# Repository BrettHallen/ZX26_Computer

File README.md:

# ZX26 Computer
I thought it might be interested to have a crack at designing a simple ZX81 clone that utilised the services of the vLA81.<br>

## [Issue 1](/Issue1)
This is my first attempt, just to see if it'll work.  I have left off the expansion connector for now.<br>

The design includes:
- Gateron low-profile keyswitches
- Dedicated cursor key cluster
- Atari-compatible joystick interface
- "FIRE" selectable between ZERO and SPACE keys
- 32KB of RAM (three schemes selectable via vLA81)
- 32KB of ROM (four switchable 8KB banks, i.e. original BASIC, modernised BASIC, ASZMIC assembler, ZX81 FORTH)
- 5V power in using a USB Type B connector (nice 'n' solid)
- Baseband video output selectable between NTSC (USA) and PAL (UK)

## vLA81
Utilising [VRetro's modern ULA replacement](https://www.vretrodesign.com/products/vla81-zx81-ula-replacement) to simplify parts & design.<br>

## Parts
Refer to the BOM for all parts.<br>

Some specific parts (i.e. footprints) I've utilised are:
- USB Type B: Same Sky UJ2-B-HR-G-TH
- RCA Jack: Kobiconn 156-0099-E
- 3.5mm Mono Jack: Same Sky SJ3-350820B
- DE9 Plug: Amphenol L717SDE09PA4CH4FC309 (or similar)

## Useful Information
- https://oldcomputer.info/8bit/zx81/ULA/ula.htm
- https://hackaday.io/project/192473-zx80zx81-remakes

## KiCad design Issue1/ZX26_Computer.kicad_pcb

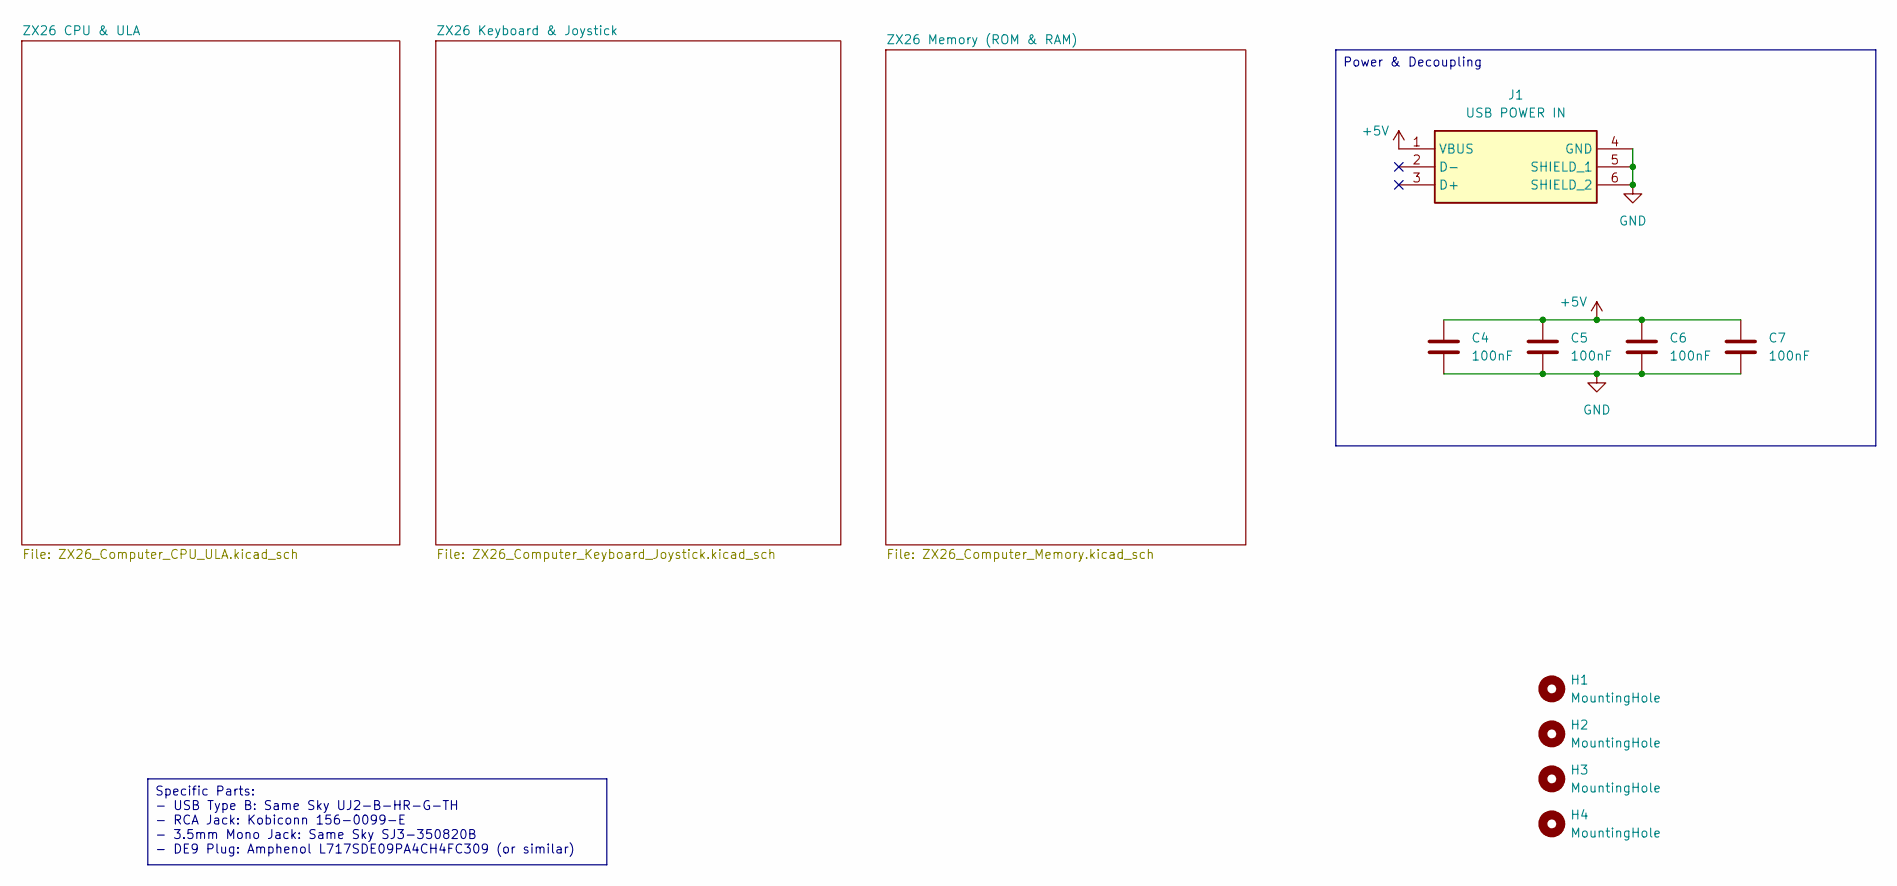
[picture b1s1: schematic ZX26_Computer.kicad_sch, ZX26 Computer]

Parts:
C4, C5, C6, C7: 100nF; C_Disc_D3.8mm_W2.6mm_P2.50mm
H1, H2, H3, H4: MountingHole; MountingHole_3.2mm_M3
J1: USB POWER IN; UJ2BHRGTH; Mouser Part Number 179-UJ2-B-HR-G-TH

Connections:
+5V: C4.1, C5.1, C6.1, C7.1, J1.1 (VBUS); also elsewhere on the board
GND: C4.2, C5.2, C6.2, C7.2, J1.4 (GND), J1.5 (SHIELD_1), J1.6 (SHIELD_2); also elsewhere on the board

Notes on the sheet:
Specific Parts: - USB Type B: Same Sky UJ2-B-HR-G-TH - RCA Jack: Kobiconn 156-0099-E - 3.5mm Mono Jack: Same Sky SJ3-350820B - DE9 Plug: Amphenol L717SDE09PA4CH4FC309 (or similar)
Power & Decoupling

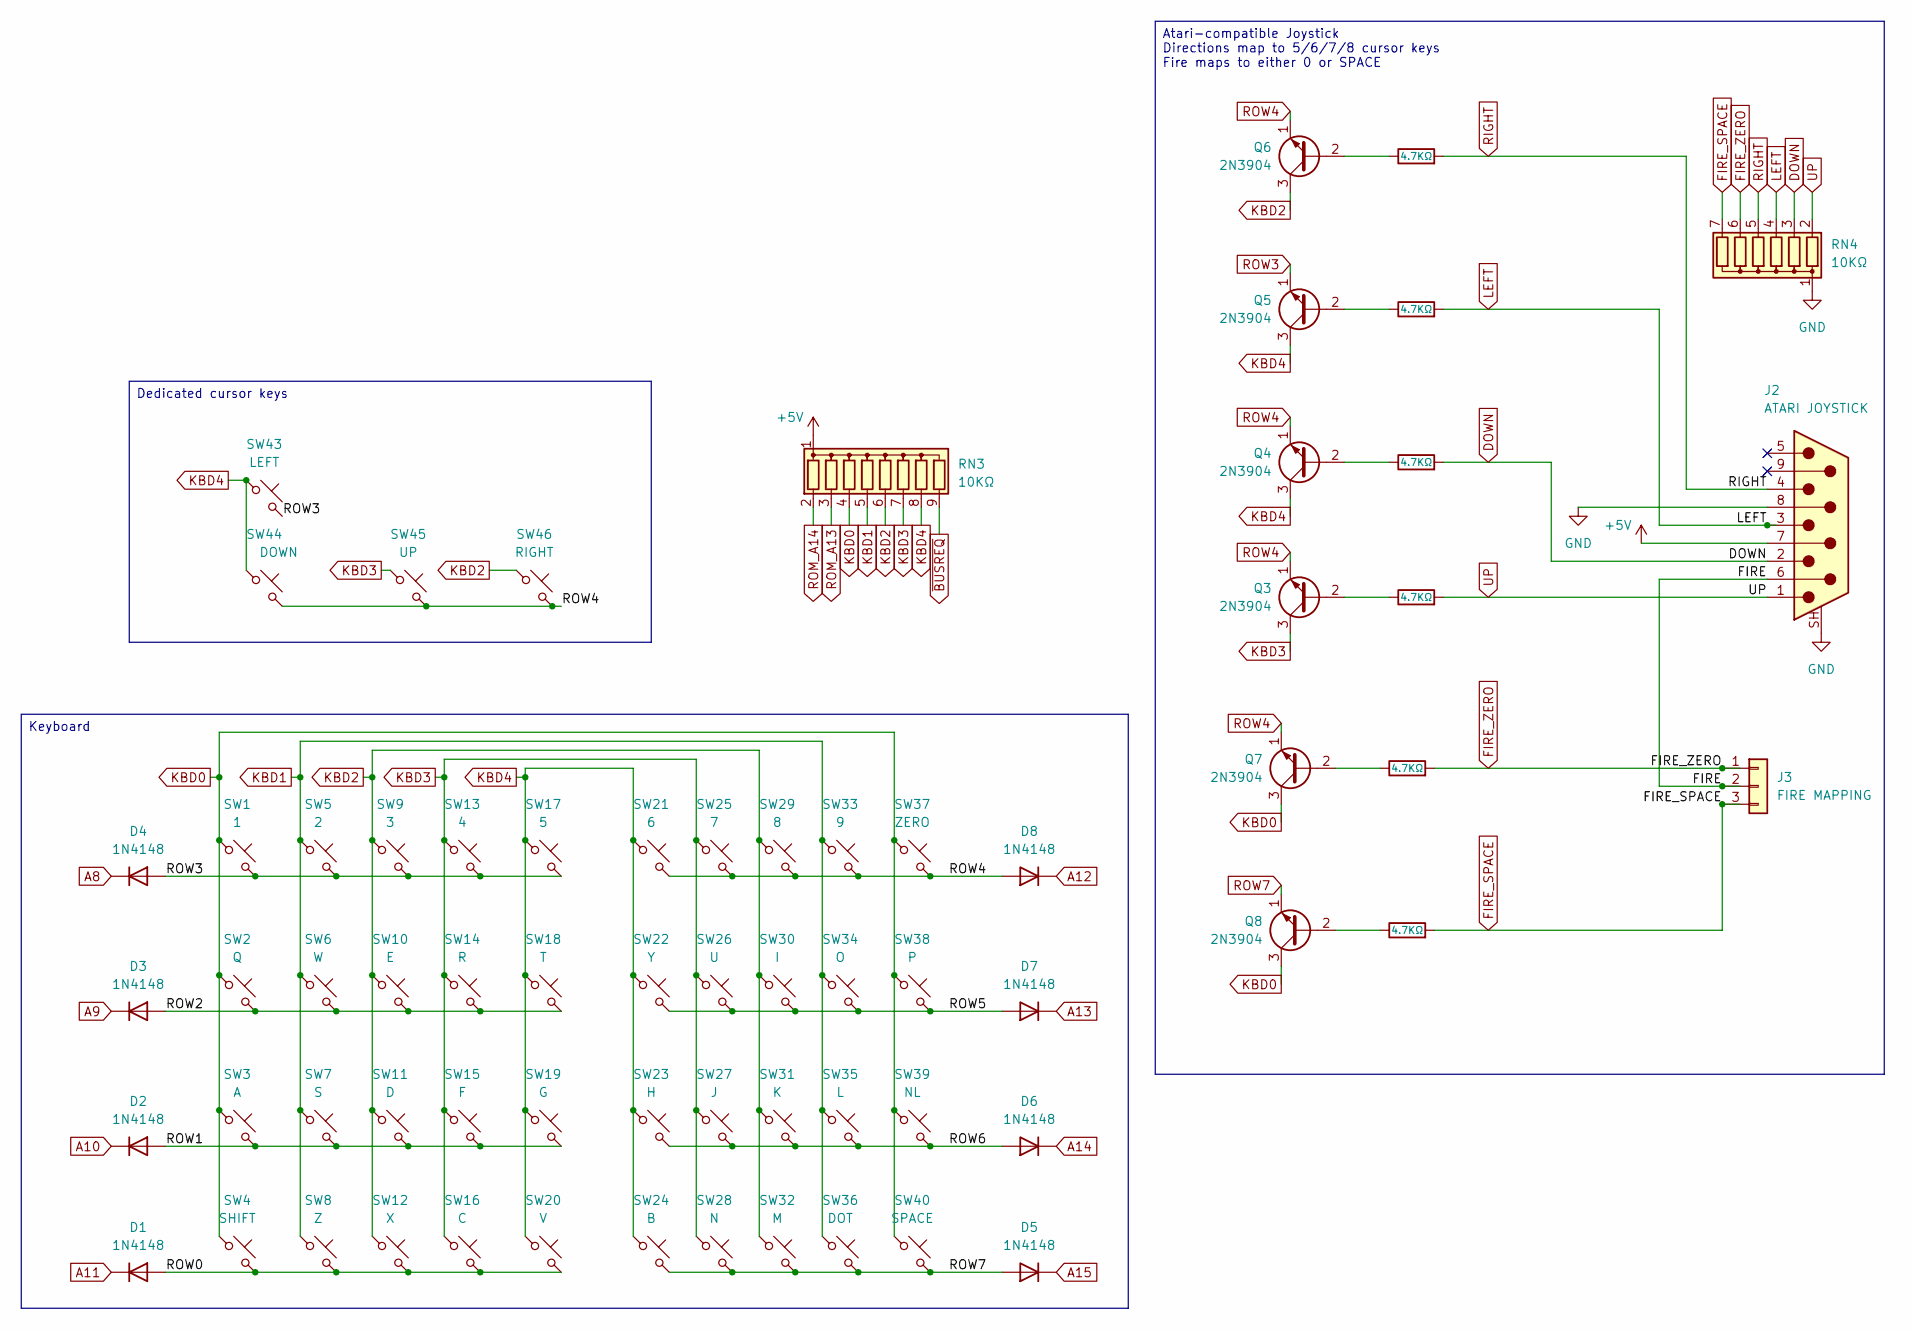
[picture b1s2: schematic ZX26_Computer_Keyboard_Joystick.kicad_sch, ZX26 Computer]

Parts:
D1, D2, D3, D4, D5, D6, D7, D8: 1N4148; D_DO-35_SOD27_P7.62mm_Horizontal
J2: ATARI JOYSTICK; DSUB-9_Pins_Horizontal_P2.77x2.84mm_EdgePinOffset7.70mm_Hou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
J3: FIRE MAPPING; PinHeader_1x03_P2.54mm_Vertical
Q3, Q4, Q5, Q6, Q7, Q8: 2N3904; TO-92_HandSolder
R27, R28, R29, R30, R31, R32: 4.7KΩ; R_Axial_DIN0207_L6.3mm_D2.5mm_P7.62mm_Horizontal
RN3: 10KΩ; R_Array_SIP9
RN4: 10KΩ; R_Array_SIP7
SW1: 1; SW_Gateron_LowProfile_THT
SW2: Q; SW_Gateron_LowProfile_THT
SW3: A; SW_Gateron_LowProfile_THT
SW4: SHIFT; SW_Gateron_LowProfile_THT
SW5: 2; SW_Gateron_LowProfile_THT
SW6: W; SW_Gateron_LowProfile_THT
SW7: S; SW_Gateron_LowProfile_THT
SW8: Z; SW_Gateron_LowProfile_THT
SW9: 3; SW_Gateron_LowProfile_THT
SW10: E; SW_Gateron_LowProfile_THT
SW11: D; SW_Gateron_LowProfile_THT
SW12: X; SW_Gateron_LowProfile_THT
SW13: 4; SW_Gateron_LowProfile_THT
SW14: R; SW_Gateron_LowProfile_THT
SW15: F; SW_Gateron_LowProfile_THT
SW16: C; SW_Gateron_LowProfile_THT
SW17: 5; SW_Gateron_LowProfile_THT
SW18: T; SW_Gateron_LowProfile_THT
SW19: G; SW_Gateron_LowProfile_THT
SW20: V; SW_Gateron_LowProfile_THT
SW21: 6; SW_Gateron_LowProfile_THT
SW22: Y; SW_Gateron_LowProfile_THT
SW23: H; SW_Gateron_LowProfile_THT
SW24: B; SW_Gateron_LowProfile_THT
SW25: 7; SW_Gateron_LowProfile_THT
SW26: U; SW_Gateron_LowProfile_THT
SW27: J; SW_Gateron_LowProfile_THT
SW28: N; SW_Gateron_LowProfile_THT
SW29: 8; SW_Gateron_LowProfile_THT
SW30: I; SW_Gateron_LowProfile_THT
SW31: K; SW_Gateron_LowProfile_THT
SW32: M; SW_Gateron_LowProfile_THT
SW33: 9; SW_Gateron_LowProfile_THT
SW34: O; SW_Gateron_LowProfile_THT
SW35: L; SW_Gateron_LowProfile_THT
SW36: DOT; SW_Gateron_LowProfile_THT
SW37: ZERO; SW_Gateron_LowProfile_THT
SW38: P; SW_Gateron_LowProfile_THT
SW39: NL; SW_Gateron_LowProfile_THT
SW40: SPACE; SW_Gateron_LowProfile_THT
SW43: LEFT; SW_Gateron_LowProfile_THT
SW44: DOWN; SW_Gateron_LowProfile_THT
SW45: UP; SW_Gateron_LowProfile_THT
SW46: RIGHT; SW_Gateron_LowProfile_THT

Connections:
+5V: J2.7, RN3.1 (common); also elsewhere on the board
/ZX26 Keyboard & Joystick/FIRE: J2.6, J3.2
/ZX26 Keyboard & Joystick/ROW0: D1.2 (A), SW4.2, SW8.2, SW12.2, SW16.2, SW20.2
/ZX26 Keyboard & Joystick/ROW1: D2.2 (A), SW3.2, SW7.2, SW11.2, SW15.2, SW19.2
/ZX26 Keyboard & Joystick/ROW2: D3.2 (A), SW2.2, SW6.2, SW10.2, SW14.2, SW18.2
/ZX26 Keyboard & Joystick/ROW5: D7.2 (A), SW22.2, SW26.2, SW30.2, SW34.2, SW38.2
/ZX26 Keyboard & Joystick/ROW6: D6.2 (A), SW23.2, SW27.2, SW31.2, SW35.2, SW39.2
A8: D4.1 (K); also elsewhere on the board
A9: D3.1 (K); also elsewhere on the board
A10: D2.1 (K); also elsewhere on the board
A11: D1.1 (K); also elsewhere on the board
A12: D8.1 (K); also elsewhere on the board
A13: D7.1 (K); also elsewhere on the board
A14: D6.1 (K); also elsewhere on the board
A15: D5.1 (K); also elsewhere on the board
DOWN: J2.2, R28.2, RN4.3 (R2)
FIRE_SPACE: J3.3, R32.2, RN4.7 (R6)
FIRE_ZERO: J3.1, R31.2, RN4.6 (R5)
GND: J2.8, J2.SH (PAD), RN4.1 (common); also elsewhere on the board
KBD0: Q7.3 (C), Q8.3 (C), RN3.4 (R3), SW1.1, SW2.1, SW3.1, SW4.1, SW37.1, SW38.1, SW39.1, SW40.1; also elsewhere on the board
KBD1: RN3.5 (R4), SW5.1, SW6.1, SW7.1, SW8.1, SW33.1, SW34.1, SW35.1, SW36.1; also elsewhere on the board
KBD2: Q6.3 (C), RN3.6 (R5), SW9.1, SW10.1, SW11.1, SW12.1, SW29.1, SW30.1, SW31.1, SW32.1, SW46.1; also elsewhere on the board
KBD3: Q3.3 (C), RN3.7 (R6), SW13.1, SW14.1, SW15.1, SW16.1, SW25.1, SW26.1, SW27.1, SW28.1, SW45.1; also elsewhere on the board
KBD4: Q4.3 (C), Q5.3 (C), RN3.8 (R7), SW17.1, SW18.1, SW19.1, SW20.1, SW21.1, SW22.1, SW23.1, SW24.1, SW43.1, SW44.1; also elsewhere on the board
LEFT: J2.3, R29.2, RN4.4 (R3)
unnamed: Q3.2 (B), R27.1
unnamed: Q4.2 (B), R28.1
unnamed: Q5.2 (B), R29.1
unnamed: Q6.2 (B), R30.1
unnamed: Q7.2 (B), R31.1
unnamed: Q8.2 (B), R32.1
RIGHT: J2.4, R30.2, RN4.5 (R4)
ROM_A13: RN3.3 (R2); also elsewhere on the board
ROM_A14: RN3.2 (R1); also elsewhere on the board
ROW3: D4.2 (A), Q5.1 (E), SW1.2, SW5.2, SW9.2, SW13.2, SW17.2, SW43.2
ROW4: D8.2 (A), Q3.1 (E), Q4.1 (E), Q6.1 (E), Q7.1 (E), SW21.2, SW25.2, SW29.2, SW33.2, SW37.2, SW44.2, SW45.2, SW46.2
ROW7: D5.2 (A), Q8.1 (E), SW24.2, SW28.2, SW32.2, SW36.2, SW40.2
UP: J2.1, R27.2, RN4.2 (R1)
~BUSREQ: RN3.9 (R8); also elsewhere on the board

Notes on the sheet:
Dedicated cursor keys
Keyboard
Atari-compatible Joystick Directions map to 5/6/7/8 cursor keys Fire maps to either 0 or SPACE

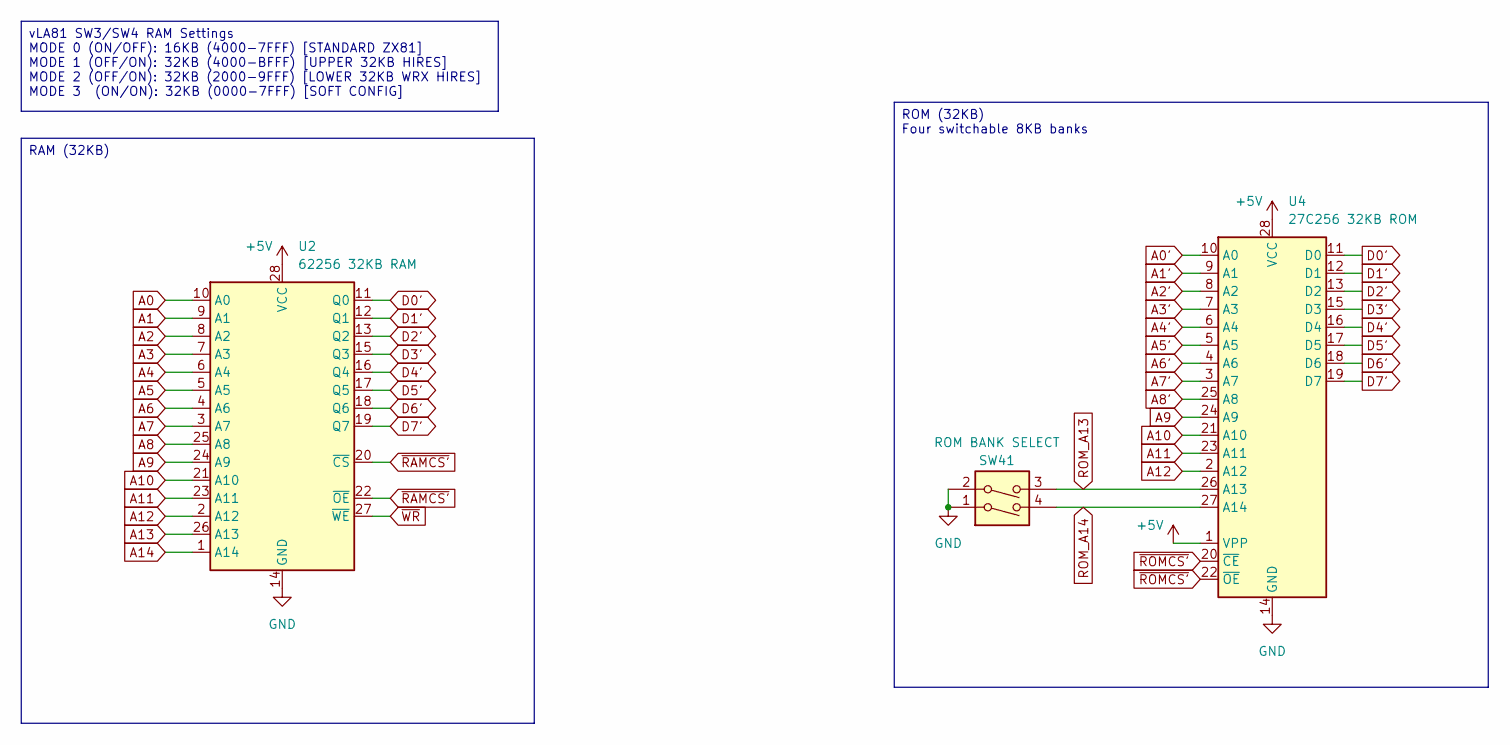
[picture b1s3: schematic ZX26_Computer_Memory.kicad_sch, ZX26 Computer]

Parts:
SW41: ROM BANK SELECT; SW_DIP_SPSTx02_Slide_9.78x7.26mm_W7.62mm_P2.54mm
U2: 62256 32KB RAM; DIP-28_W15.24mm
U4: 27C256 32KB ROM; DIP-28_W15.24mm

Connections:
+5V: U2.28 (VCC), U4.1 (VPP), U4.28 (VCC); also elsewhere on the board
A0: U2.10 (A0); also elsewhere on the board
A0': U4.10 (A0); also elsewhere on the board
A1: U2.9 (A1); also elsewhere on the board
A1': U4.9 (A1); also elsewhere on the board
A2: U2.8 (A2); also elsewhere on the board
A2': U4.8 (A2); also elsewhere on the board
A3: U2.7 (A3); also elsewhere on the board
A3': U4.7 (A3); also elsewhere on the board
A4: U2.6 (A4); also elsewhere on the board
A4': U4.6 (A4); also elsewhere on the board
A5: U2.5 (A5); also elsewhere on the board
A5': U4.5 (A5); also elsewhere on the board
A6: U2.4 (A6); also elsewhere on the board
A6': U4.4 (A6); also elsewhere on the board
A7: U2.3 (A7); also elsewhere on the board
A7': U4.3 (A7); also elsewhere on the board
A8: U2.25 (A8); also elsewhere on the board
A8': U4.25 (A8); also elsewhere on the board
A9: U2.24 (A9), U4.24 (A9); also elsewhere on the board
A10: U2.21 (A10), U4.21 (A10); also elsewhere on the board
A11: U2.23 (A11), U4.23 (A11); also elsewhere on the board
A12: U2.2 (A12), U4.2 (A12); also elsewhere on the board
A13: U2.26 (A13); also elsewhere on the board
A14: U2.1 (A14); also elsewhere on the board
D0': U2.11 (Q0), U4.11 (D0); also elsewhere on the board
D1': U2.12 (Q1), U4.12 (D1); also elsewhere on the board
D2': U2.13 (Q2), U4.13 (D2); also elsewhere on the board
D3': U2.15 (Q3), U4.15 (D3); also elsewhere on the board
D4': U2.16 (Q4), U4.16 (D4); also elsewhere on the board
D5': U2.17 (Q5), U4.17 (D5); also elsewhere on the board
D6': U2.18 (Q6), U4.18 (D6); also elsewhere on the board
D7': U2.19 (Q7), U4.19 (D7); also elsewhere on the board
GND: SW41.1, SW41.2, U2.14 (GND), U4.14 (GND); also elsewhere on the board
ROM_A13: SW41.3, U4.26 (A13); also elsewhere on the board
ROM_A14: SW41.4, U4.27 (A14); also elsewhere on the board
~RAMCS': U2.20 (~CS), U2.22 (~OE); also elsewhere on the board
~ROMCS': U4.20 (~CE), U4.22 (~OE); also elsewhere on the board
~WR: U2.27 (~WE); also elsewhere on the board

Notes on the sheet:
RAM (32KB)
ROM (32KB) Four switchable 8KB banks
vLA81 SW3/SW4 RAM Settings MODE 0 (ON/OFF): 16KB (4000-7FFF) [STANDARD ZX81] MODE 1 (OFF/ON): 32KB (4000-BFFF) [UPPER 32KB HIRES] MODE 2 (OFF/ON): 32KB (2000-9FFF) [LOWER 32KB WRX HIRES] MODE 3 (ON/ON): 32KB (0000-7FFF) [SOFT CONFIG]

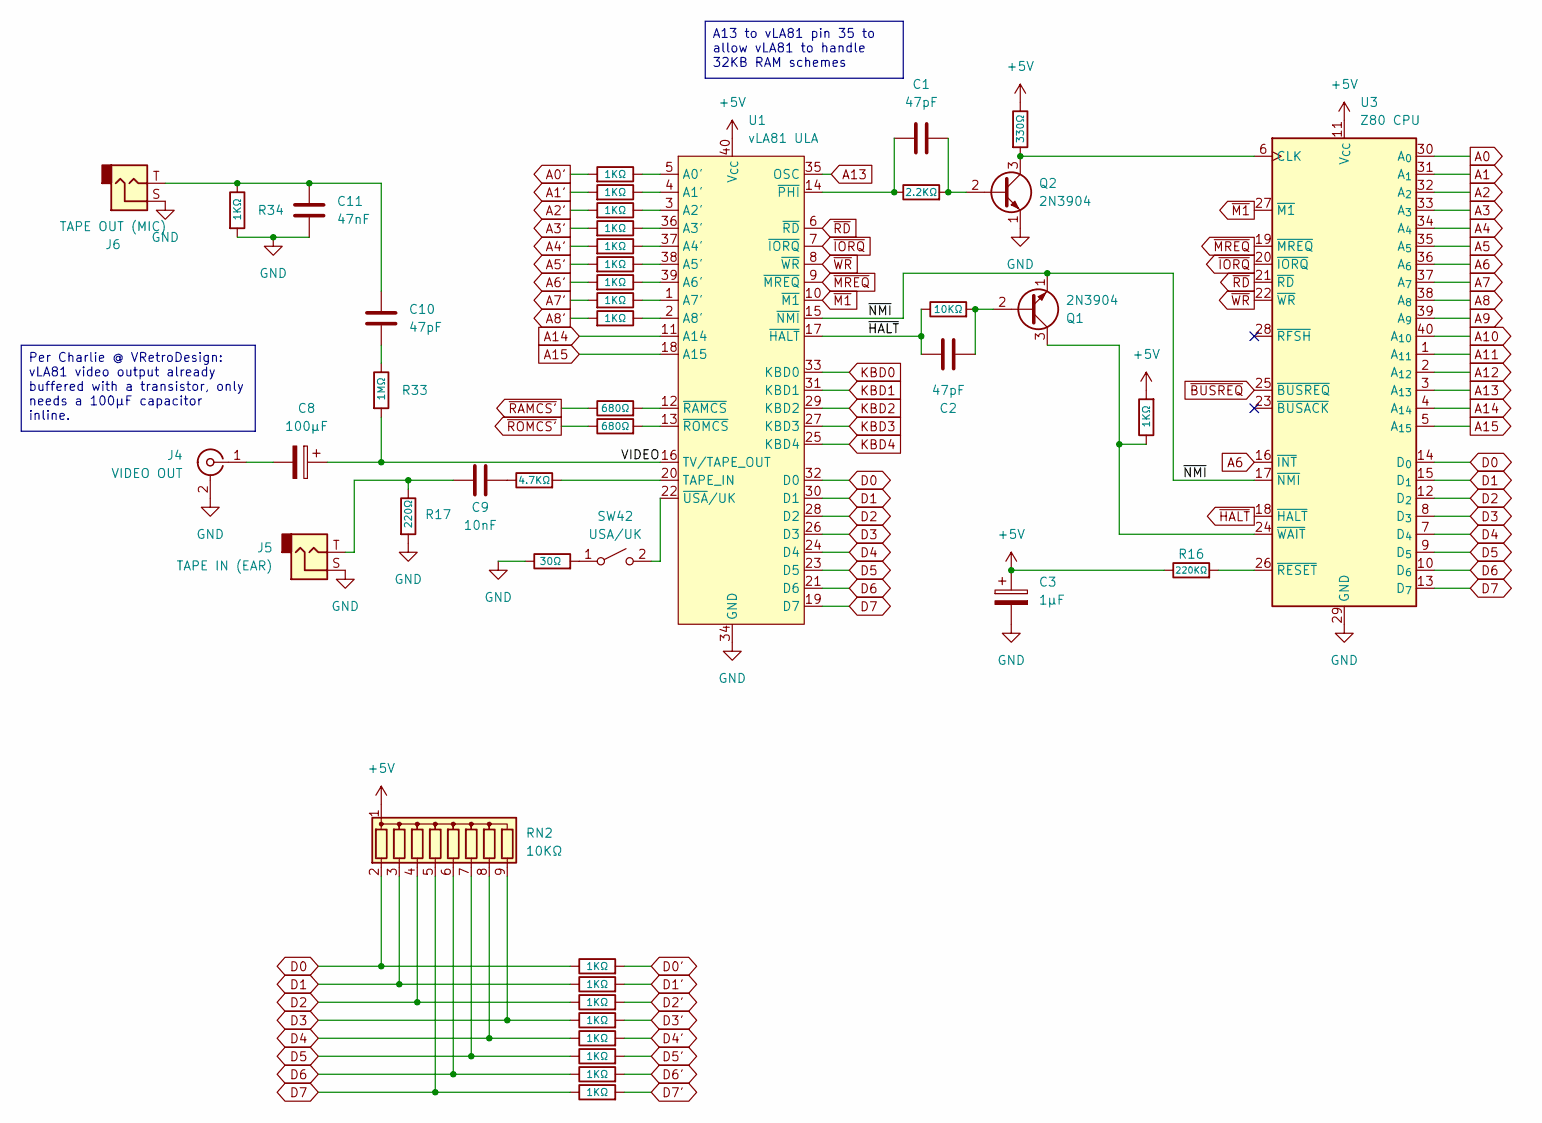
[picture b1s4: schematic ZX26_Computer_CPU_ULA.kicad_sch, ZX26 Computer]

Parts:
C1, C2, C10: 47pF; C_Disc_D3.8mm_W2.6mm_P2.50mm
C3: 1µF; CP_Radial_D5.0mm_P2.50mm
C8: 100µF; CP_Radial_D5.0mm_P2.50mm
C9: 10nF; C_Disc_D3.8mm_W2.6mm_P2.50mm
C11: 47nF; C_Disc_D3.8mm_W2.6mm_P2.50mm
J4: VIDEO OUT; 1560099E
J5: TAPE IN (EAR); SJ3350820BTR
J6: TAPE OUT (MIC); SJ3350820BTR
Q1, Q2: 2N3904; TO-92_HandSolder
R1, R2, R3, R4, R5, R6, R7, R8, R9, R15, R18, R19, R20, R21, R22, R23, R24, R25, R34: 1KΩ; R_Axial_DIN0207_L6.3mm_D2.5mm_P7.62mm_Horizontal
R10: 2.2KΩ; R_Axial_DIN0207_L6.3mm_D2.5mm_P7.62mm_Horizontal
R11: 330Ω; R_Axial_DIN0207_L6.3mm_D2.5mm_P7.62mm_Horizontal
R12, R13: 680Ω; R_Axial_DIN0207_L6.3mm_D2.5mm_P7.62mm_Horizontal
R14: 10KΩ; R_Axial_DIN0207_L6.3mm_D2.5mm_P7.62mm_Horizontal
R16: 220KΩ; R_Axial_DIN0207_L6.3mm_D2.5mm_P7.62mm_Horizontal
R17: 220Ω; R_Axial_DIN0207_L6.3mm_D2.5mm_P7.62mm_Horizontal
R26: 30Ω; R_Axial_DIN0207_L6.3mm_D2.5mm_P7.62mm_Horizontal
R33: 1MΩ; R_Axial_DIN0207_L6.3mm_D2.5mm_P7.62mm_Horizontal
R43: 4.7KΩ; R_Axial_DIN0207_L6.3mm_D2.5mm_P7.62mm_Horizontal
RN2: 10KΩ; R_Array_SIP9
SW42: USA/UK; PinHeader_1x02_P2.54mm_Vertical
U1: vLA81 ULA; DIP-40_W15.24mm
U3: Z80 CPU; DIP-40_W15.24mm

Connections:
+5V: C3.1, R11.1, R15.2, R16.1, RN2.1 (common), U1.40 (V_{CC}), U3.11 (V_{CC}); also elsewhere on the board
/ZX26 CPU & ULA/VIDEO: C8.1, R33.2, U1.16 (TV/TAPE_OUT)
/ZX26 CPU & ULA/~NMI: Q1.1 (E), U1.15 (~NMI), U3.17 (~NMI)
A0: U3.30 (A_{0}); also elsewhere on the board
A0': R1.2; also elsewhere on the board
A1: U3.31 (A_{1}); also elsewhere on the board
A1': R2.2; also elsewhere on the board
A2: U3.32 (A_{2}); also elsewhere on the board
A2': R3.2; also elsewhere on the board
A3: U3.33 (A_{3}); also elsewhere on the board
A3': R4.2; also elsewhere on the board
A4: U3.34 (A_{4}); also elsewhere on the board
A4': R5.2; also elsewhere on the board
A5: U3.35 (A_{5}); also elsewhere on the board
A5': R6.2; also elsewhere on the board
A6: U3.16 (~INT), U3.36 (A_{6}); also elsewhere on the board
A6': R7.2; also elsewhere on the board
A7: U3.37 (A_{7}); also elsewhere on the board
A7': R8.2; also elsewhere on the board
A8: U3.38 (A_{8}); also elsewhere on the board
A8': R9.2; also elsewhere on the board
A9: U3.39 (A_{9}); also elsewhere on the board
A10: U3.40 (A_{10}); also elsewhere on the board
A11: U3.1 (A_{11}); also elsewhere on the board
A12: U3.2 (A_{12}); also elsewhere on the board
A13: U1.35 (OSC), U3.3 (A_{13}); also elsewhere on the board
A14: U1.11 (A14), U3.4 (A_{14}); also elsewhere on the board
A15: U1.18 (A15), U3.5 (A_{15}); also elsewhere on the board
D0: R18.1, RN2.2 (R1), U1.32 (D0), U3.14 (D_{0})
D0': R18.2; also elsewhere on the board
D1: R19.1, RN2.3 (R2), U1.30 (D1), U3.15 (D_{1})
D1': R19.2; also elsewhere on the board
D2: R20.1, RN2.4 (R3), U1.28 (D2), U3.12 (D_{2})
D2': R20.2; also elsewhere on the board
D3: R21.1, RN2.9 (R8), U1.26 (D3), U3.8 (D_{3})
D3': R21.2; also elsewhere on the board
D4: R22.1, RN2.8 (R7), U1.24 (D4), U3.7 (D_{4})
D4': R22.2; also elsewhere on the board
D5: R23.1, RN2.7 (R6), U1.23 (D5), U3.9 (D_{5})
D5': R23.2; also elsewhere on the board
D6: R24.1, RN2.6 (R5), U1.21 (D6), U3.10 (D_{6})
D6': R24.2; also elsewhere on the board
D7: R25.1, RN2.5 (R4), U1.19 (D7), U3.13 (D_{7})
D7': R25.2; also elsewhere on the board
GND: C3.2, C11.2, J4.2 (Ext), J5.S, J6.S, Q2.1 (E), R17.2, R26.1, R34.2, U1.34 (GND), U3.29 (GND); also elsewhere on the board
KBD0: U1.33 (KBD0); also elsewhere on the board
KBD1: U1.31 (KBD1); also elsewhere on the board
KBD2: U1.29 (KBD2); also elsewhere on the board
KBD3: U1.27 (KBD3); also elsewhere on the board
KBD4: U1.25 (KBD4); also elsewhere on the board
unnamed: C9.1, J5.T, R17.1
unnamed: C9.2, R43.1
unnamed: C10.1, C11.1, J6.T, R34.1
unnamed: C10.2, R33.1
unnamed: C8.2, J4.1 (In)
unnamed: C2.2, Q1.2 (B), R14.2
unnamed: Q1.3 (C), R15.1, U3.24 (~WAIT)
unnamed: C1.2, Q2.2 (B), R10.2
unnamed: Q2.3 (C), R11.2, U3.6 (CLK)
unnamed: R26.2, SW42.1 (A)
unnamed: SW42.2 (B), U1.22 (~USA/UK)
unnamed: R1.1, U1.5 (A0')
unnamed: R2.1, U1.4 (A1')
unnamed: R3.1, U1.3 (A2')
unnamed: R4.1, U1.36 (A3')
unnamed: R5.1, U1.37 (A4')
unnamed: R6.1, U1.38 (A5')
unnamed: R7.1, U1.39 (A6')
unnamed: R8.1, U1.1 (A7')
unnamed: R9.1, U1.2 (A8')
unnamed: R43.2, U1.20 (TAPE_IN)
unnamed: C1.1, R10.1, U1.14 (~PHI)
unnamed: R13.2, U1.12 (~RAMCS)
unnamed: R12.2, U1.13 (~ROMCS)
unnamed: R16.2, U3.26 (~RESET)
~BUSREQ: U3.25 (~BUSREQ); also elsewhere on the board
~HALT: C2.1, R14.1, U1.17 (~HALT), U3.18 (~HALT)
~IORQ: U1.7 (~IORQ), U3.20 (~IORQ)
~M1: U1.10 (~M1), U3.27 (~M1)
~MREQ: U1.9 (~MREQ), U3.19 (~MREQ)
~RAMCS': R13.1; also elsewhere on the board
~RD: U1.6 (~RD), U3.21 (~RD)
~ROMCS': R12.1; also elsewhere on the board
~WR: U1.8 (~WR), U3.22 (~WR); also elsewhere on the board

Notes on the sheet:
A13 to vLA81 pin 35 to allow vLA81 to handle 32KB RAM schemes
Per Charlie @ VRetroDesign: vLA81 video output already buffered with a transistor, only needs a 100µF capacitor inline.

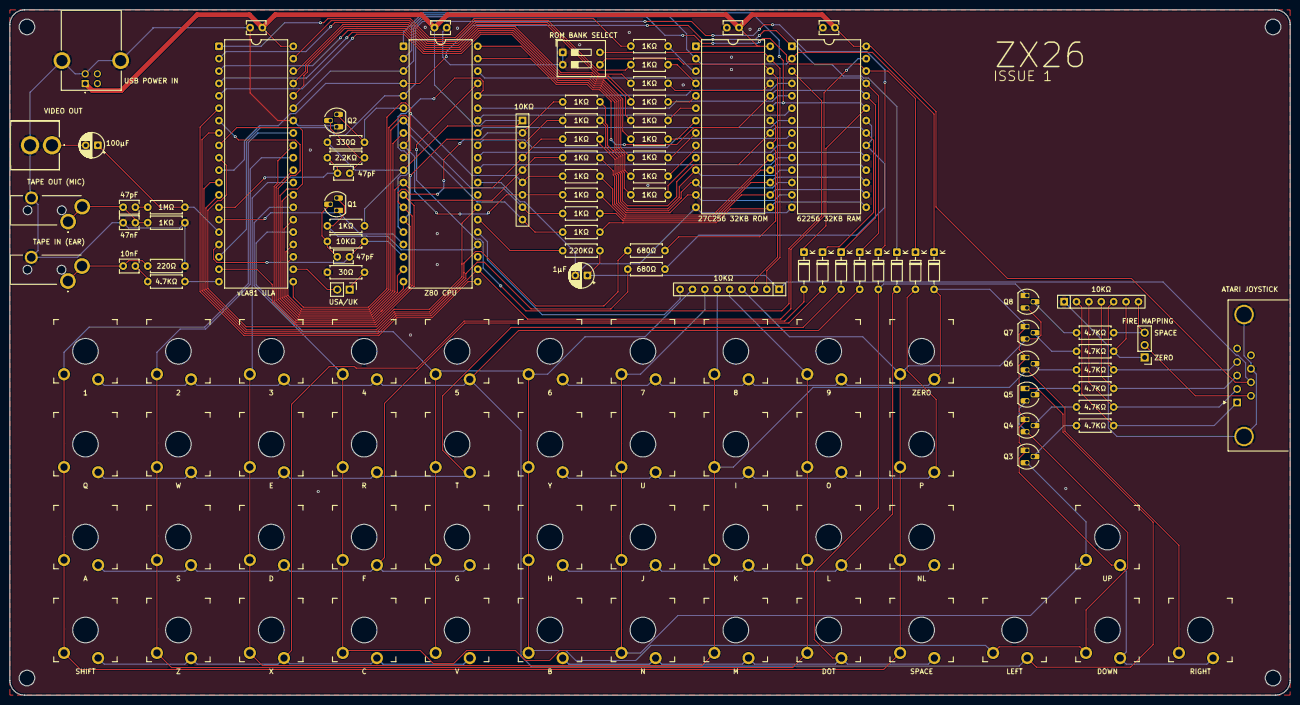
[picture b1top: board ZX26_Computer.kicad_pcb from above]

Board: 2 copper layers, 262.5 x 140.5 mm, 125 parts (0 on the bottom side), 107 nets.

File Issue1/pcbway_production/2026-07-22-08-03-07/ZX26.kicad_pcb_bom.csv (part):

Designator,Quantity,Value,Footprint,Package,MPN,DNP,Mount_Type,Description,KiLib_Generator,Sim.Device,Sim.Pins,Height,Mouser Part Number,Mouser Price/Stock,Manufacturer_Name
"C1, C10, C2",3,47pF,C_Disc_D3.8mm_W2.6mm_P2.50mm,,,,tht,Unpolarized capacitor,capacitor/THT/other,,,,,,
C11,1,47nF,C_Disc_D3.8mm_W2.6mm_P2.50mm,,,,tht,Unpolarized capacitor,capacitor/THT/other,,,,,,
C3,1,1µF,CP_Radial_D5.0mm_P2.50mm,,,,tht,Polarized capacitor,capacitor/THT/other,,,,,,
"C4, C5, C6, C7",4,100nF,C_Disc_D3.8mm_W2.6mm_P2.50mm,,,,tht,Unpolarized capacitor,capacitor/THT/other,,,,,,
C8,1,100µF,CP_Radial_D5.0mm_P2.50mm,,,,tht,Polarized capacitor,capacitor/THT/other,,,,,,
C9,1,10nF,C_Disc_D3.8mm_W2.6mm_P2.50mm,,,,tht,Unpolarized capacitor,capacitor/THT/other,,,,,,
"D1, D2, D3, D4, D5, D6, D7, D8",8,1N4148,D_DO-35_SOD27_P7.62mm_Horizontal,,,,tht,Diode,diode/THT,D,1=K 2=A,,,,
J1,1,USB POWER IN,UJ2BHRGTH,,UJ2-B-HR-G-TH,,tht,"Type B, USB 2.0, 480 Mbps, 5 Vdc, 1.5 A, Right Angle, Through Hole Mounting Style, Through Hole Contact Pin Type, Board Lock, 0.6 in Plating Thickness, Black Insulator, Pick & Place, USB Receptacle",,,,11.1,179-UJ2-B-HR-G-TH,https://www.mouser.co.uk/ProductDetail/Same-Sky/UJ2-B-HR-G-T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,Same Sky
J2,1,ATARI JOYSTICK,DSUB-9_Pins_Horizontal_P2.77x2.84mm_EdgePinOffset7.70mm_Housed_MountingHolesOffset9.12mm,,,,tht,"9-pin D-SUB connector, pins (male), Mounting Hole",connector/D_sub,,,,,,
J3,1,SPACE/0,PinHeader_1x03_P2.54mm_Vertical,,,,tht,"Generic connector, single row, 01x03, script generated (kicad-library-utils/schlib/autogen/connector/)",connector/pin_header_socket,,,,,,
J4,1,VIDEO OUT,1560099E,,,,tht,"coaxial connector (BNC, SMA, SMB, SMC, Cinch/RCA, LEMO, ...)",,,,,,,
J5,1,TAPE IN,SJ3350820BTR,,,,tht,"Audio Jack, 2 Poles (Mono / TS)",,,,,,,
J6,1,TAPE OUT,SJ3350820BTR,,,,tht,"Audio Jack, 2 Poles (Mono / TS)",,,,,,,
"Q1, Q2, Q3, Q4, Q5, Q6, Q7, Q8",8,2N3904,TO-92_HandSolder,,,,tht,"0.2A Ic, 40V Vce, Small Signal NPN Transistor, TO-92",,NPN,1=E 2=B 3=C,,,,
"R1, R15, R18, R19, R2, R20, R21, R22, R23, R24, R25, R3, R34, R4, R5, R6, R7, R8, R9",19,1KΩ,R_Axial_DIN0207_L6.3mm_D2.5mm_P7.62mm_Horizontal,,,,tht,Resistor,resistor/THT,,,,,,
R10,1,2.2KΩ,R_Axial_DIN0207_L6.3mm_D2.5mm_P7.62mm_Horizontal,,,,tht,Resistor,resistor/THT,,,,,,
R11,1,330Ω,R_Axial_DIN0207_L6.3mm_D2.5mm_P7.62mm_Horizontal,,,,tht,Resistor,resistor/THT,,,,,,
"R12, R13",2,680Ω,R_Axial_DIN0207_L6.3mm_D2.5mm_P7.62mm_Horizontal,,,,tht,Resistor,resistor/THT,,,,,,
R14,1,10KΩ,R_Axial_DIN0207_L6.3mm_D2.5mm_P7.62mm_Horizontal,,,,tht,Resistor,resistor/THT,,,,,,
R16,1,220KΩ,R_Axial_DIN0207_L6.3mm_D2.5mm_P7.62mm_Horizontal,,,,tht,Resistor,resistor/THT,,,,,,
R17,1,220Ω,R_Axial_DIN0207_L6.3mm_D2.5mm_P7.62mm_Horizontal,,,,tht,Resistor,resistor/THT,,,,,,
R26,1,30Ω,R_Axial_DIN0207_L6.3mm_D2.5mm_P7.62mm_Horizontal,,,,tht,Resistor,resistor/THT,,,,,,
"R27, R28, R29, R30, R31, R32, R43",7,4.7KΩ,R_Axial_DIN0207_L6.3mm_D2.5mm_P7.62mm_Horizontal,,,,tht,Resistor,resistor/THT,,,,,,
R33,1,1MΩ,R_Axial_DIN0207_L6.3mm_D2.5mm_P7.62mm_Horizontal,,,,tht,Resistor,resistor/THT,,,,,,
"RN2, RN3",2,10KΩ,R_Array_SIP9,,,,tht,"8 resistor network, star topology, bussed resistors, small symbol",resistor/array_SIP_THT,,,,,,
RN4,1,10KΩ,R_Array_SIP7,,,,tht,"6 resistor network, star topology, bussed resistors, small symbol",resistor/array_SIP_THT,,,,,,
SW1,1,1,SW_Gateron_LowProfile_THT,,,,tht,"Push button switch, normally open, two pins, 45° tilted",,,,,,,
SW10,1,E,SW_Gateron_LowProfile_THT,,,,tht,"Push button switch, normally open, two pins, 45° tilted",,,,,,,
SW11,1,D,SW_Gateron_LowProfile_THT,,,,tht,"Push button switch, normally open, two pins, 45° tilted",,,,,,,
SW12,1,X,SW_Gateron_LowProfile_THT,,,,tht,"Push button switch, normally open, two pins, 45° tilted",,,,,,,
SW13,1,4,SW_Gateron_LowProfile_THT,,,,tht,"Push button switch, normally open, two pins, 45° tilted",,,,,,,
SW14,1,R,SW_Gateron_LowProfile_THT,,,,tht,"Push button switch, normally open, two pins, 45° tilted",,,,,,,
SW15,1,F,SW_Gateron_LowProfile_THT,,,,tht,"Push button switch, normally open, two pins, 45° tilted",,,,,,,
SW16,1,C,SW_Gateron_LowProfile_THT,,,,tht,"Push button switch, normally open, two pins, 45° tilted",,,,,,,
SW17,1,5,SW_Gateron_LowProfile_THT,,,,tht,"Push button switch, normally open, two pins, 45° tilted",,,,,,,
SW18,1,T,SW_Gateron_LowProfile_THT,,,,tht,"Push button switch, normally open, two pins, 45° tilted",,,,,,,
SW19,1,G,SW_Gateron_LowProfile_THT,,,,tht,"Push button switch, normally open, two pins, 45° tilted",,,,,,,
SW2,1,Q,SW_Gateron_LowProfile_THT,,,,tht,"Push button switch, normally open, two pins, 45° tilted",,,,,,,
SW20,1,V,SW_Gateron_LowProfile_THT,,,,tht,"Push button switch, normally open, two pins, 45° tilted",,,,,,,
SW21,1,6,SW_Gateron_LowProfile_THT,,,,tht,"Push button switch, normally open, two pins, 45° tilted",,,,,,,
SW22,1,Y,SW_Gateron_LowProfile_THT,,,,tht,"Push button switch, normally open, two pins, 45° tilted",,,,,,,
SW23,1,H,SW_Gateron_LowProfile_THT,,,,tht,"Push button switch, normally open, two pins, 45° tilted",,,,,,,
SW24,1,B,SW_Gateron_LowProfile_THT,,,,tht,"Push button switch, normally open, two pins, 45° tilted",,,,,,,
SW25,1,7,SW_Gateron_LowProfile_THT,,,,tht,"Push button switch, normally open, two pins, 45° tilted",,,,,,,
SW26,1,U,SW_Gateron_LowProfile_THT,,,,tht,"Push button switch, normally open, two pins, 45° tilted",,,,,,,
SW27,1,J,SW_Gateron_LowProfile_THT,,,,tht,"Push button switch, normally open, two pins, 45° tilted",,,,,,,
SW28,1,N,SW_Gateron_LowProfile_THT,,,,tht,"Push button switch, normally open, two pins, 45° tilted",,,,,,,
SW29,1,8,SW_Gateron_LowProfile_THT,,,,tht,"Push button switch, normally open, two pins, 45° tilted",,,,,,,
SW3,1,A,SW_Gateron_LowProfile_THT,,,,tht,"Push button switch, normally open, two pins, 45° tilted",,,,,,,
SW30,1,I,SW_Gateron_LowProfile_THT,,,,tht,"Push button switch, normally open, two pins, 45° tilted",,,,,,,
SW31,1,K,SW_Gateron_LowProfile_THT,,,,tht,"Push button switch, normally open, two pins, 45° tilted",,,,,,,
SW32,1,M,SW_Gateron_LowProfile_THT,,,,tht,"Push button switch, normally open, two pins, 45° tilted",,,,,,,
SW33,1,9,SW_Gateron_LowProfile_THT,,,,tht,"Push button switch, normally open, two pins, 45° tilted",,,,,,,
SW34,1,O,SW_Gateron_LowProfile_THT,,,,tht,"Push button switch, normally open, two pins, 45° tilted",,,,,,,
SW35,1,L,SW_Gateron_LowProfile_THT,,,,tht,"Push button switch, normally open, two pins, 45° tilted",,,,,,,
SW36,1,DOT,SW_Gateron_LowProfile_THT,,,,tht,"Push button switch, normally open, two pins, 45° tilted",,,,,,,
SW37,1,ZERO,SW_Gateron_LowProfile_THT,,,,tht,"Push button switch, normally open, two pins, 45° tilted",,,,,,,
SW38,1,P,SW_Gateron_LowProfile_THT,,,,tht,"Push button switch, normally open, two pins, 45° tilted",,,,,,,
SW39,1,NL,SW_Gateron_LowProfile_THT,,,,tht,"Push button switch, normally open, two pins, 45° tilted",,,,,,,
SW4,1,SHIFT,SW_Gateron_LowProfile_THT,,,,tht,"Push button switch, normally open, two pins, 45° tilted",,,,,,,
SW40,1,SPACE,SW_Gateron_LowProfile_THT,,,,tht,"Push button switch, normally open, two pins, 45° tilted",,,,,,,
SW41,1,ROM BANK SELECT,SW_DIP_SPSTx02_Slide_9.78x7.26mm_W7.62mm_P2.54mm,,,,tht,"2x DIP Switch, Single Pole Single Throw (SPST) switch, small symbol",button_switch/DIP,,,,,,
SW42,1,USA/UK,PinHeader_1x02_P2.54mm_Vertical,,,,tht,Single Pole Single Throw (SPST) switch,connector/pin_header_socket,,,,,,
SW43,1,LEFT,SW_Gateron_LowProfile_THT,,,,tht,"Push button switch, normally open, two pins, 45° tilted",,,,,,,
SW44,1,DOWN,SW_Gateron_LowProfile_THT,,,,tht,"Push button switch, normally open, two pins, 45° tilted",,,,,,,
SW45,1,UP,SW_Gateron_LowProfile_THT,,,,tht,"Push button switch, normally open, two pins, 45° tilted",,,,,,,
SW46,1,RIGHT,SW_Gateron_LowProfile_THT,,,,tht,"Push button switch, normally open, two pins, 45° tilted",,,,,,,
SW5,1,2,SW_Gateron_LowProfile_THT,,,,tht,"Push button switch, normally open, two pins, 45° tilted",,,,,,,
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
